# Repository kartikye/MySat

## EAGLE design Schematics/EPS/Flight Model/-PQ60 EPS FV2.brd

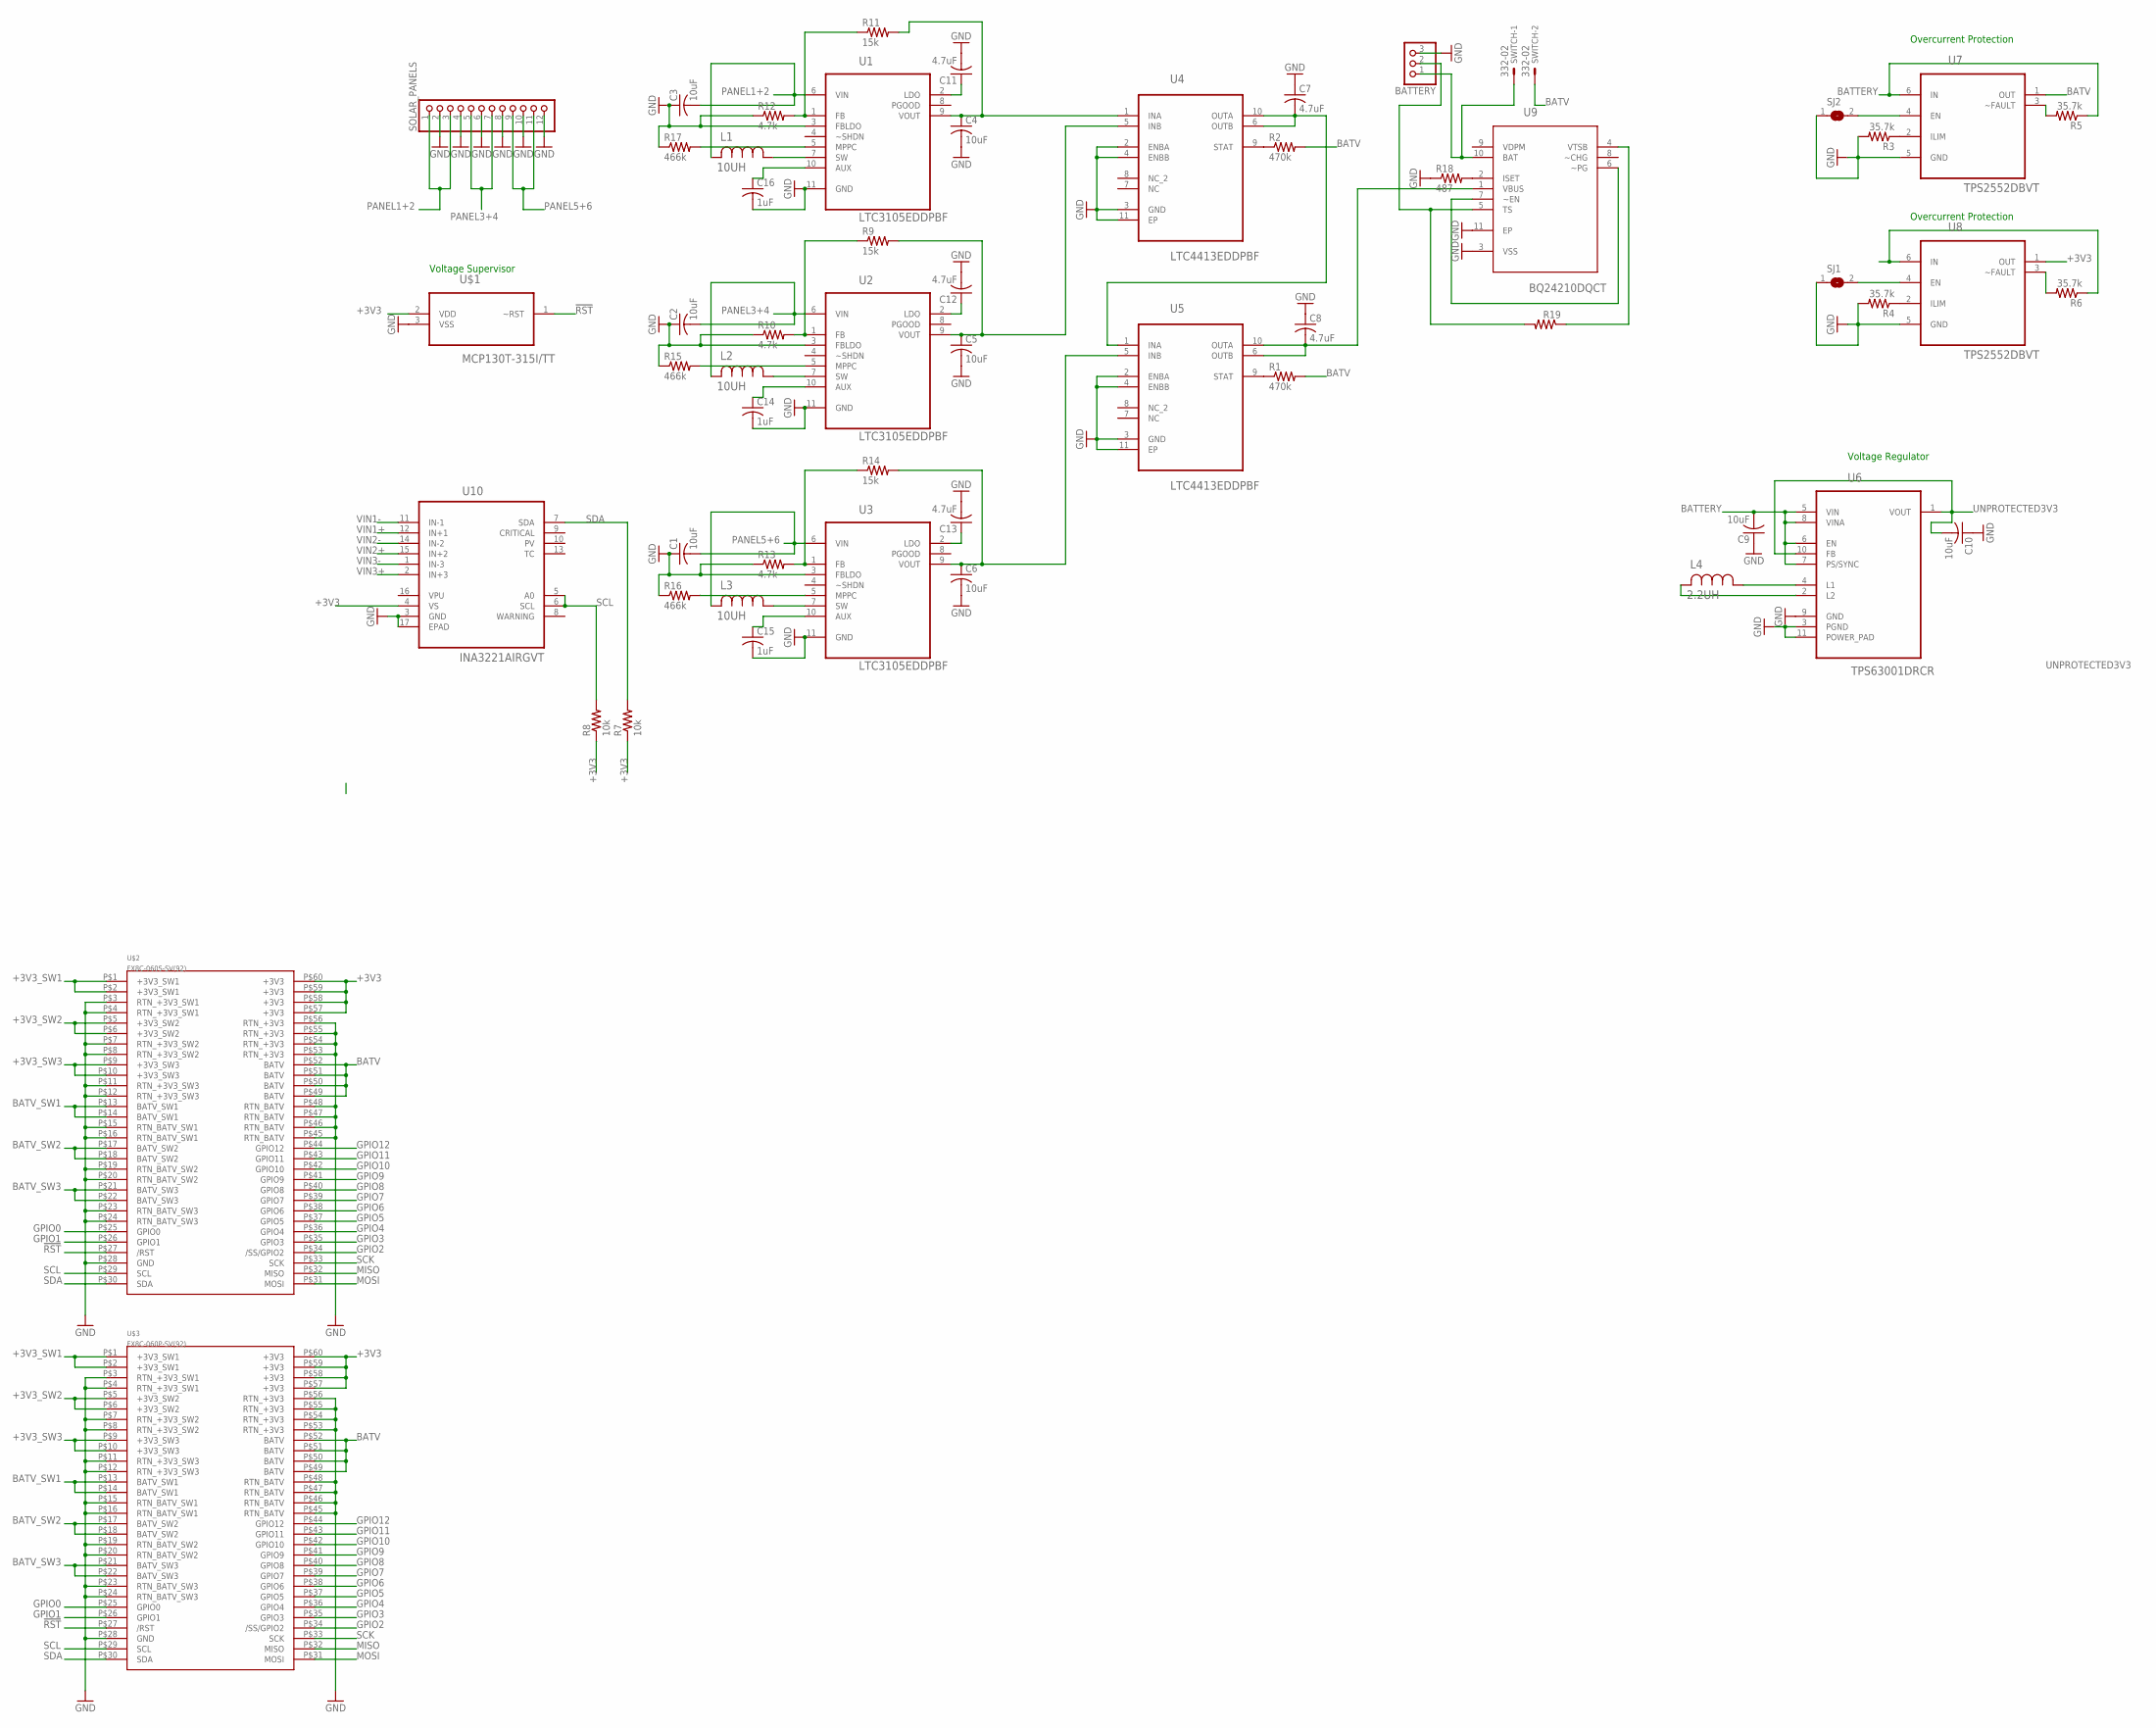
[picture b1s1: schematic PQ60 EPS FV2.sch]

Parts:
BATTERY: PINHD-1X3; 1X03
C1, C2, C3, C4, C5, C6, C9, C10: 10uF; C0805
C7, C8, C11, C12, C13: 4.7uF; C0805
C14, C15, C16: 1uF; C0805
L1, L2, L3: 10UH; IND_ELL6XH
L4: 2.2UH; IND_ELL3FU
R1, R2: 470k; R0805
R3, R4, R5, R6: 35.7k; R0805
R7, R8: 10k; R0805
R9, R11, R14: 15k; R0805
R10, R12, R13: 4.7k; R0805
R15, R16, R17: 466k; R0805
R18: 487; R0805
R19: R-US_R0805; R0805
SJ1, SJ2: SJ
SOLAR_PANELS: PINHD-1X12-CB; 1X12-CB
SWITCH: 332-02
U1, U2, U3: LTC3105EDDPBF; DFN300X300X80-11N
U4, U5: LTC4413EDDPBF; DFN300X300X80-11N
U6: TPS63001DRCR; SON50P300X300X100-11N
U7, U8: TPS2552DBVT; SOT95P280X145-6N
U9: BQ24210DQCT; SON50P200X300X80-11N
U10: INA3221AIRGVT; QFN65P400X400X80-17N
U$1: MCP130T-315I/TT; SOT95P237X112-3N
U$2: FX8C-060S-SV(92)
U$3: FX8C-060P-SV(92)

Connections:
!RST: U$1.1 (~RST), U$2.P$27 (/RST), U$3.P$27 (/RST)
+3V3: R7.1, R8.1, U8.1 (OUT), U10.4 (VS), U$1.2 (VDD), U$2.P$57 (+3V3), U$2.P$58 (+3V3), U$2.P$59 (+3V3), U$2.P$60 (+3V3), U$3.P$57 (+3V3), U$3.P$58 (+3V3), U$3.P$59 (+3V3), U$3.P$60 (+3V3)
+3V3_SW1: U$2.P$1 (+3V3_SW1), U$2.P$2 (+3V3_SW1), U$3.P$1 (+3V3_SW1), U$3.P$2 (+3V3_SW1)
+3V3_SW2: U$2.P$5 (+3V3_SW2), U$2.P$6 (+3V3_SW2), U$3.P$5 (+3V3_SW2), U$3.P$6 (+3V3_SW2)
+3V3_SW3: U$2.P$9 (+3V3_SW3), U$2.P$10 (+3V3_SW3), U$3.P$9 (+3V3_SW3), U$3.P$10 (+3V3_SW3)
BATTERY: C9.2, R5.1, U6.5 (VIN), U6.6 (EN), U6.7 (PS/SYNC), U6.8 (VINA), U7.6 (IN)
BATV: R1.2, R2.2, SWITCH.2, U7.1 (OUT), U$2.P$49 (BATV), U$2.P$50 (BATV), U$2.P$51 (BATV), U$2.P$52 (BATV), U$3.P$49 (BATV), U$3.P$50 (BATV), U$3.P$51 (BATV), U$3.P$52 (BATV)
BATV_SW1: U$2.P$13 (BATV_SW1), U$2.P$14 (BATV_SW1), U$3.P$13 (BATV_SW1), U$3.P$14 (BATV_SW1)
BATV_SW2: U$2.P$17 (BATV_SW2), U$2.P$18 (BATV_SW2), U$3.P$17 (BATV_SW2), U$3.P$18 (BATV_SW2)
BATV_SW3: U$2.P$21 (BATV_SW3), U$2.P$22 (BATV_SW3), U$3.P$21 (BATV_SW3), U$3.P$22 (BATV_SW3)
GND: BATTERY.3, C1.1, C2.1, C3.1, C4.2, C5.2, C6.2, C7.1, C8.1, C9.1, C10.1, C11.2, C12.2, C13.2, C14.2, C15.2, C16.2, R3.2, R4.2, R10.1, R12.1, R13.1, R15.1, R16.1, R17.1, R18.1, SJ1.1, SJ2.1, SOLAR_PANELS.2, SOLAR_PANELS.4, SOLAR_PANELS.6, SOLAR_PANELS.8, SOLAR_PANELS.10, SOLAR_PANELS.12, U1.3 (FBLDO), U1.11 (GND), U2.3 (FBLDO), U2.11 (GND), U3.3 (FBLDO), U3.11 (GND), U4.2 (ENBA), U4.3 (GND), U4.4 (ENBB), U4.11 (EP), U5.2 (ENBA), U5.3 (GND), U5.4 (ENBB), U5.11 (EP), U6.3 (PGND), U6.9 (GND), U6.11 (POWER_PAD), U7.5 (GND), U8.5 (GND), U9.3 (VSS), U9.11 (EP), U10.3 (GND), U10.17 (EPAD), U$1.3 (VSS), U$2.P$3 (RTN_+3V3_SW1), U$2.P$4 (RTN_+3V3_SW1), U$2.P$7 (RTN_+3V3_SW2), U$2.P$8 (RTN_+3V3_SW2), U$2.P$11 (RTN_+3V3_SW3), U$2.P$12 (RTN_+3V3_SW3), U$2.P$15 (RTN_BATV_SW1), U$2.P$16 (RTN_BATV_SW1), U$2.P$19 (RTN_BATV_SW2), U$2.P$20 (RTN_BATV_SW2), U$2.P$23 (RTN_BATV_SW3), U$2.P$24 (RTN_BATV_SW3), U$2.P$28 (GND), U$2.P$45 (RTN_BATV), U$2.P$46 (RTN_BATV), U$2.P$47 (RTN_BATV), U$2.P$48 (RTN_BATV), U$2.P$53 (RTN_+3V3), U$2.P$54 (RTN_+3V3), U$2.P$55 (RTN_+3V3), U$2.P$56 (RTN_+3V3), U$3.P$45 (RTN_BATV), U$3.P$46 (RTN_BATV), U$3.P$47 (RTN_BATV), U$3.P$48 (RTN_BATV), U$3.P$53 (RTN_+3V3), U$3.P$54 (RTN_+3V3), U$3.P$55 (RTN_+3V3), U$3.P$56 (RTN_+3V3)
GPIO0: U$2.P$25 (GPIO0), U$3.P$25 (GPIO0)
GPIO1: U$2.P$26 (GPIO1), U$3.P$26 (GPIO1)
GPIO2: U$2.P$34 (/SS/GPIO2), U$3.P$34 (/SS/GPIO2)
GPIO3: U$2.P$35 (GPIO3), U$3.P$35 (GPIO3)
GPIO4: U$2.P$36 (GPIO4), U$3.P$36 (GPIO4)
GPIO5: U$2.P$37 (GPIO5), U$3.P$37 (GPIO5)
GPIO6: U$2.P$38 (GPIO6), U$3.P$38 (GPIO6)
GPIO7: U$2.P$39 (GPIO7), U$3.P$39 (GPIO7)
GPIO8: U$2.P$40 (GPIO8), U$3.P$40 (GPIO8)
GPIO9: U$2.P$41 (GPIO9), U$3.P$41 (GPIO9)
GPIO10: U$2.P$42 (GPIO10), U$3.P$42 (GPIO10)
GPIO11: U$2.P$43 (GPIO11), U$3.P$43 (GPIO11)
GPIO12: U$2.P$44 (GPIO12), U$3.P$44 (GPIO12)
MISO: U$2.P$32 (MISO), U$3.P$32 (MISO)
MOSI: U$2.P$31 (MOSI), U$3.P$31 (MOSI)
unnamed: L2.1, U2.7 (SW)
unnamed: L3.1, U3.7 (SW)
unnamed: L1.1, U1.7 (SW)
unnamed: L4.1, U6.4 (L1)
unnamed: C4.1, R11.2, U1.9 (VOUT), U4.1 (INA)
unnamed: C5.1, R9.2, U2.9 (VOUT), U4.5 (INB)
unnamed: C6.1, R14.2, U3.9 (VOUT), U5.5 (INB)
unnamed: R4.1, U8.2 (ILIM)
unnamed: C7.2, U4.6 (OUTB), U4.10 (OUTA), U5.1 (INA)
unnamed: R1.1, U5.9 (STAT)
unnamed: R2.1, U4.9 (STAT)
unnamed: L4.2, U6.2 (L2)
unnamed: R3.1, U7.2 (ILIM)
unnamed: R5.2, U7.3 (~FAULT)
unnamed: R6.2, U8.3 (~FAULT)
unnamed: SJ1.2, U8.4 (EN)
unnamed: SJ2.2, U7.4 (EN)
unnamed: C11.1, U1.2 (LDO)
unnamed: C12.1, U2.2 (LDO)
unnamed: C13.1, U3.2 (LDO)
unnamed: C14.1, U2.10 (AUX)
unnamed: C15.1, U3.10 (AUX)
unnamed: C16.1, U1.10 (AUX)
unnamed: R9.1, R10.2, U2.1 (FB)
unnamed: R13.2, R14.1, U3.1 (FB)
unnamed: R11.1, R12.2, U1.1 (FB)
unnamed: R15.2, U2.5 (MPPC)
unnamed: R16.2, U3.5 (MPPC)
unnamed: R17.2, U1.5 (MPPC)
unnamed: C8.2, U5.6 (OUTB), U5.10 (OUTA), U9.1 (VBUS)
unnamed: U9.6 (~PG), U9.7 (~EN)
unnamed: R18.2, U9.2 (ISET)
unnamed: BATTERY.1, SWITCH.1, U9.10 (BAT)
unnamed: BATTERY.2, R19.2, U9.5 (TS)
unnamed: R19.1, U9.4 (VTSB)
PANEL1+2: C3.2, L1.2, SOLAR_PANELS.1, SOLAR_PANELS.3, U1.6 (VIN)
PANEL3+4: C2.2, L2.2, SOLAR_PANELS.5, SOLAR_PANELS.7, U2.6 (VIN)
PANEL5+6: C1.2, L3.2, SOLAR_PANELS.9, SOLAR_PANELS.11, U3.6 (VIN)
RTN_+3V3_SW1: U$3.P$3 (RTN_+3V3_SW1), U$3.P$4 (RTN_+3V3_SW1)
RTN_+3V3_SW2: U$3.P$7 (RTN_+3V3_SW2), U$3.P$8 (RTN_+3V3_SW2)
RTN_+3V3_SW3: U$3.P$11 (RTN_+3V3_SW3), U$3.P$12 (RTN_+3V3_SW3)
RTN_BATV_SW1: U$3.P$15 (RTN_BATV_SW1), U$3.P$16 (RTN_BATV_SW1)
RTN_BATV_SW2: U$3.P$19 (RTN_BATV_SW2), U$3.P$20 (RTN_BATV_SW2)
RTN_BATV_SW3: U$3.P$23 (RTN_BATV_SW3), U$3.P$24 (RTN_BATV_SW3)
SCK: U$2.P$33 (SCK), U$3.P$33 (SCK)
UNPROTECTED3V3: C10.2, R6.1, U6.1 (VOUT), U6.10 (FB), U8.6 (IN)
VIN1+: U10.12 (IN+1)
VIN1-: U10.11 (IN-1)
VIN2+: U10.15 (IN+2)
VIN2-: U10.14 (IN-2)
VIN3+: U10.2 (IN+3)
VIN3-: U10.1 (IN-3)
VPU: U10.16 (VPU)

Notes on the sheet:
Voltage Regulator
Voltage Supervisor
Overcurrent Protection

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
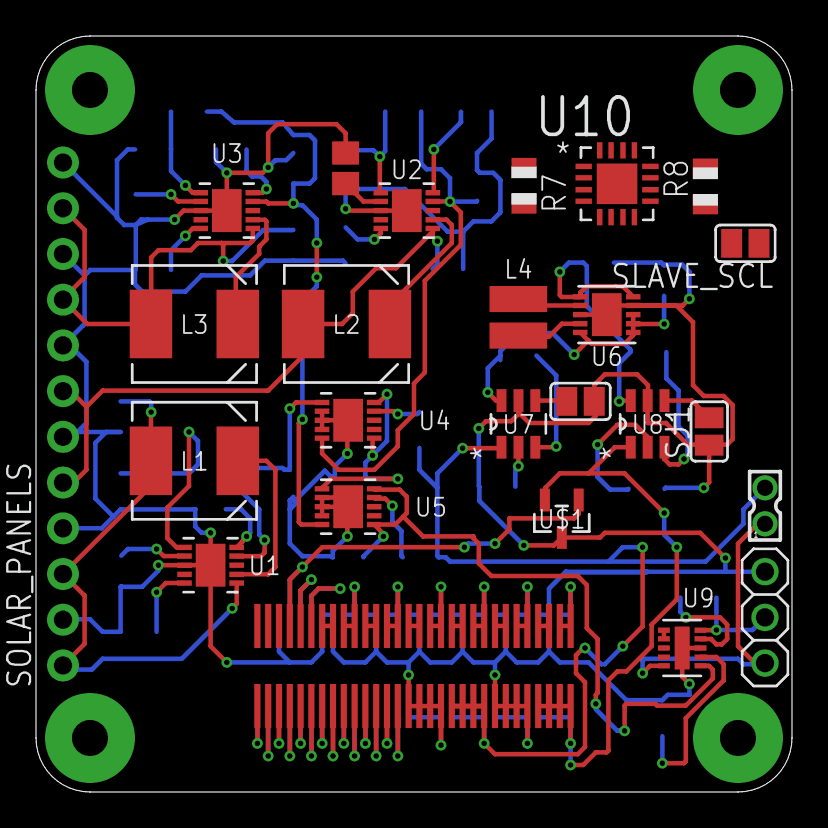
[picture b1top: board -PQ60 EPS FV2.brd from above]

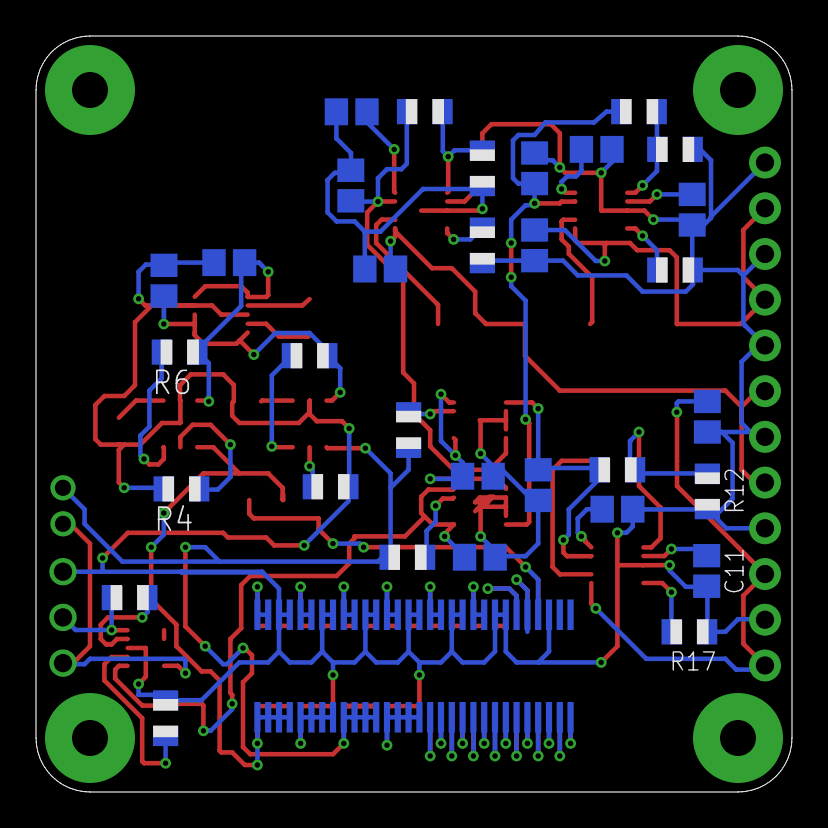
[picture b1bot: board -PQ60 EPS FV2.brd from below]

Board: 2 copper layers, 42.0 x 42.0 mm, 58 parts (33 on the bottom side), 77 nets.

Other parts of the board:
SLAVE_SCL: SJ

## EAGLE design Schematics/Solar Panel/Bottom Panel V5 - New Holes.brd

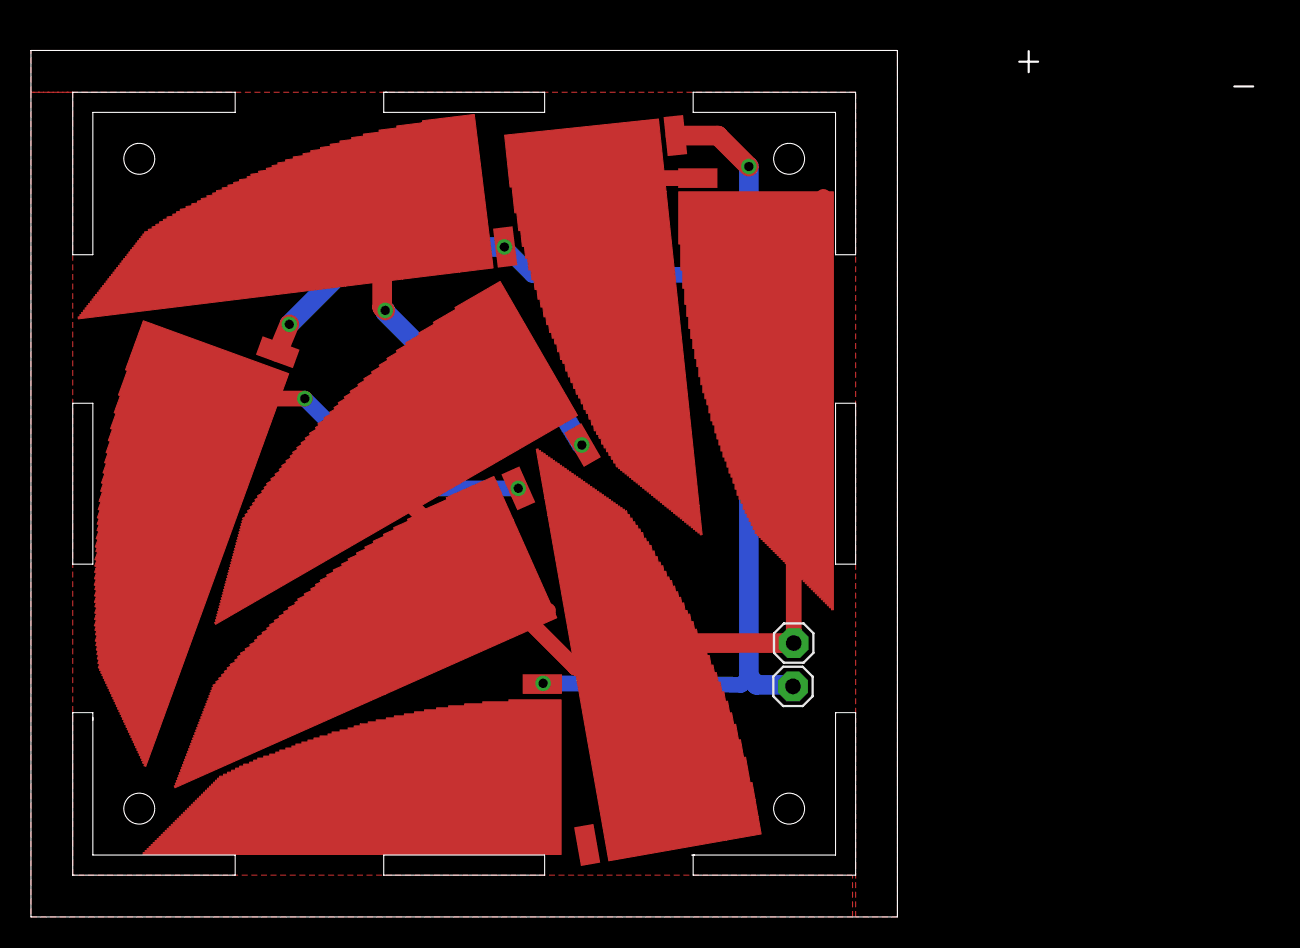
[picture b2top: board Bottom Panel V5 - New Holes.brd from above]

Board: 2 copper layers, 56.0 x 56.0 mm, 18 parts (0 on the bottom side), 6 nets.

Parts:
E$1, E$2, E$3, E$4, E$5, E$6, E$7, E$19: TRISOLX
E$8, E$9, E$10, E$11, E$12, E$13, E$14, E$15: SMD1,27-2,54
E$16, E$17: 1X01

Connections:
S$1: E$3.P$1, E$4.P$1, E$5.P$1, E$16.1, E$19.P$1
S$3: E$1.P$1, E$15.1
S$4: E$8.1, E$11.1, E$13.1, E$14.1, E$17.1
S$5: E$2.P$1, E$9.1
S$8: E$7.P$1, E$10.1
S$10: E$6.P$1, E$12.1
